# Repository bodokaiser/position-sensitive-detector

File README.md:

# Position-sensitive detector

Position-sensitive detector using the Hamamatsu S5991-01 position-sensitive photodiode.

| Parameter | Value |
| --------- | ----- |
| Spatial resolution | 2 um |
| Bandwidth | 1400 kHz |
| Input voltage | +- 15 V |
| Output voltage | +- 12 V |

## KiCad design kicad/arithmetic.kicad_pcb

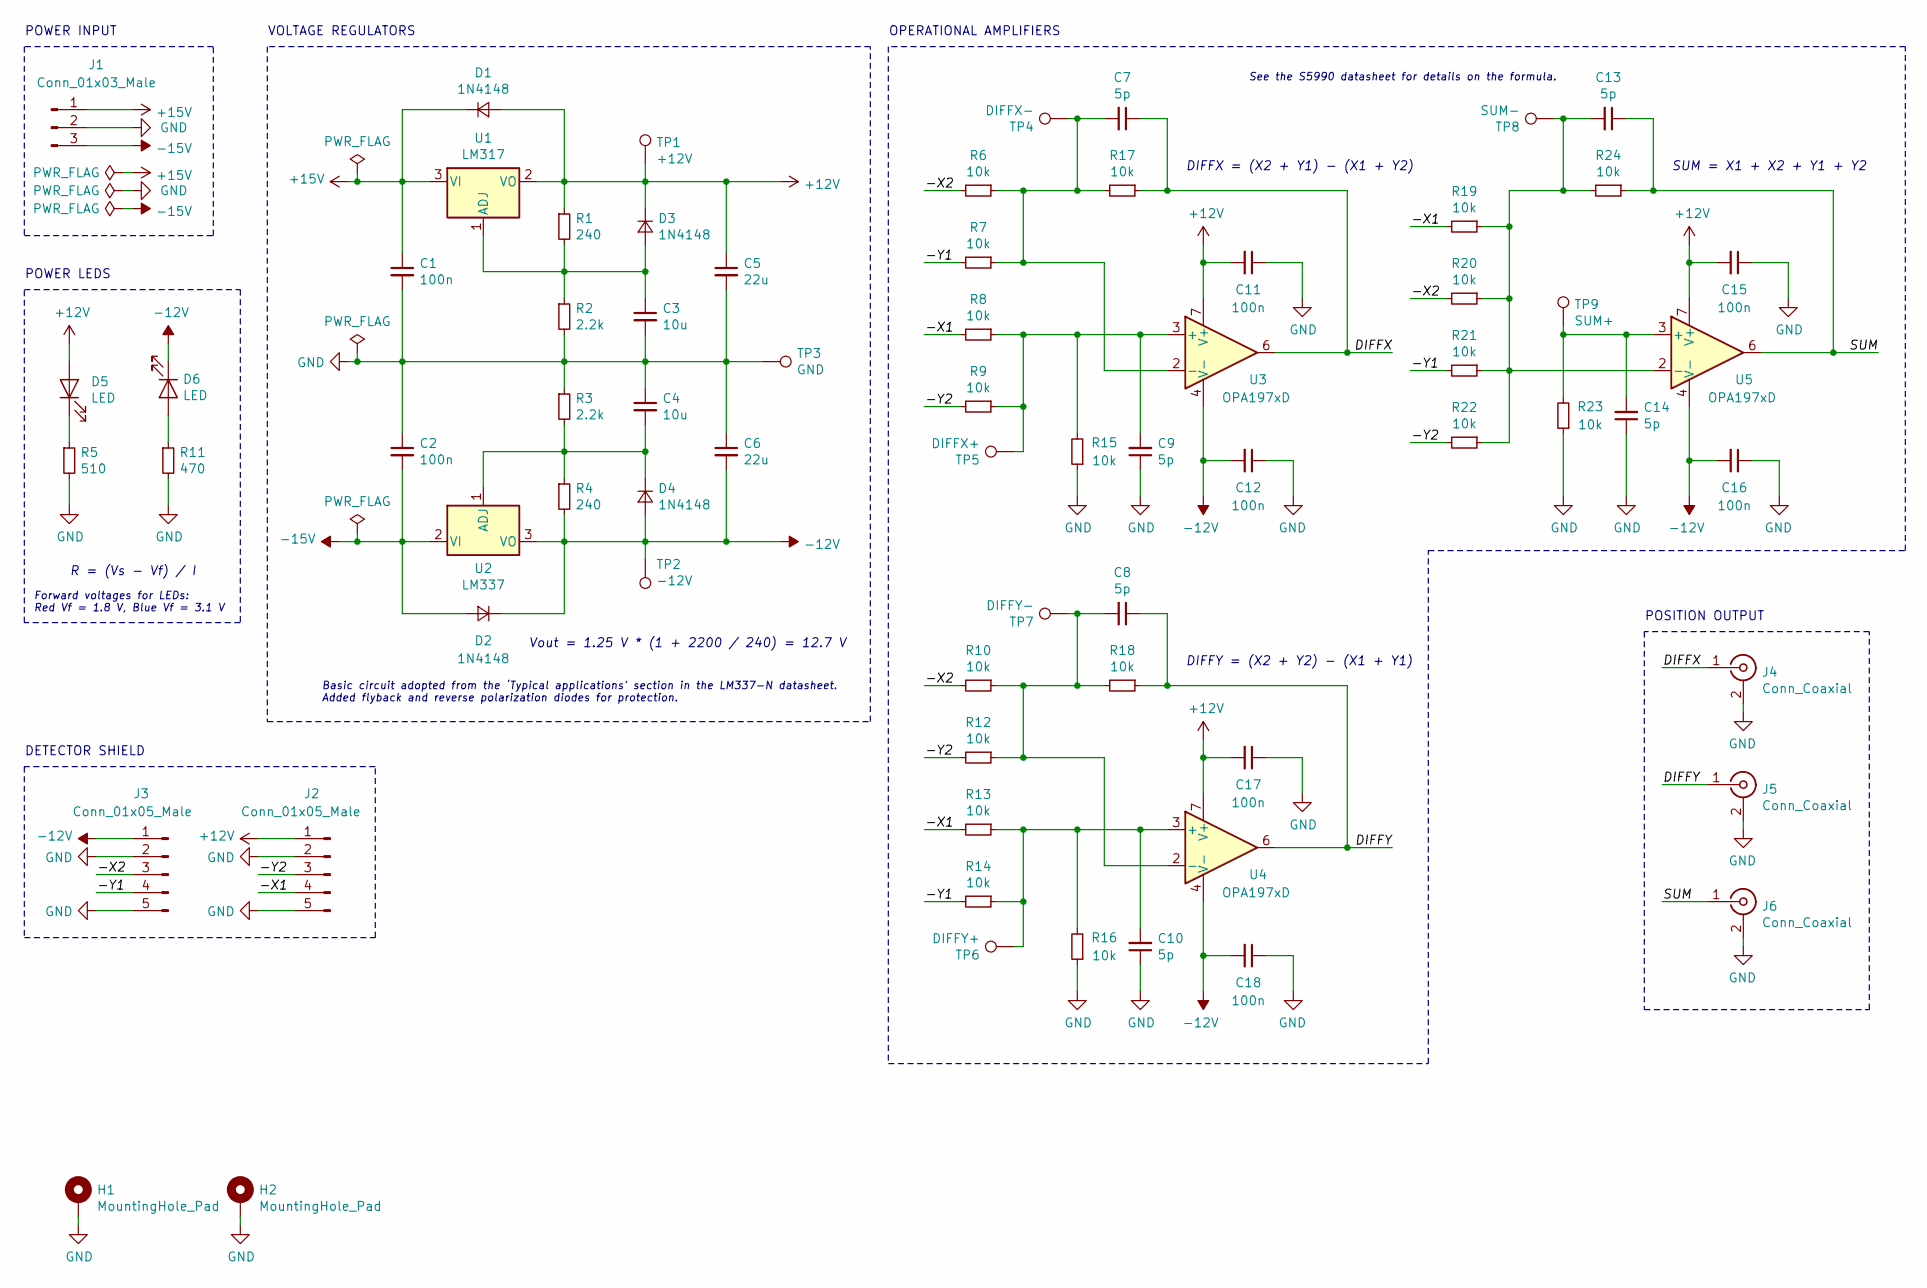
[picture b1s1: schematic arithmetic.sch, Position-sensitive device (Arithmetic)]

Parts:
C1, C2, C11, C12, C15, C16, C17, C18: 100n; C_0603_1608Metric
C3, C4: 10u; C_1210_3225Metric
C5, C6: 22u; C_1210_3225Metric
C7, C8, C9, C10, C13, C14: 5p; C_0603_1608Metric
D1, D2, D3, D4: 1N4148; D_SOD-123
D5, D6: LED; LED_0603_1608Metric
H1, H2: MountingHole_Pad; MountingHole_2.7mm_M2.5_Pad
J1: Conn_01x03_Male; FanPinHeader_1x03_P2.54mm_Vertical
J2, J3: Conn_01x05_Male; PinHeader_1x05_P2.54mm_Vertical
J4, J5, J6: Conn_Coaxial; SMA_Molex_73251-2120_EdgeMount
R1, R4: 240; R_1210_3225Metric
R2, R3: 2.2k; R_1210_3225Metric
R5: 510; R_0603_1608Metric
R6, R7, R8, R9, R10, R12, R13, R14, R15, R16, R17, R18, R19, R20, R21, R22, R23, R24: 10k; R_0603_1608Metric
R11: 470; R_0603_1608Metric
TP1: +12V; TestPoint_Pad_D1.0mm
TP2: -12V; TestPoint_Pad_D1.0mm
TP3: GND; TestPoint_Pad_D1.0mm
TP4: DIFFX-; TestPoint_Pad_D1.0mm
TP5: DIFFX+; TestPoint_Pad_D1.0mm
TP6: DIFFY+; TestPoint_Pad_D1.0mm
TP7: DIFFY-; TestPoint_Pad_D1.0mm
TP8: SUM-; TestPoint_Pad_D1.0mm
TP9: SUM+; TestPoint_Pad_D1.0mm
U1: LM317; SOT-223-3_TabPin2
U2: LM337; SOT-223-3_TabPin2
U3, U4, U5: OPA197xD; SOIC-8_3.9x4.9mm_P1.27mm

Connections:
+12V: C5.1, C11.2, C15.2, C17.2, D1.2 (A), D3.1 (K), D5.2 (A), J2.1, R1.1, TP1.1, U1.2 (VO), U3.7 (V+), U4.7 (V+), U5.7 (V+); also elsewhere on the board
+15V: C1.1, D1.1 (K), J1.1, U1.3 (VI)
-12V: C6.2, C12.2, C16.2, C18.2, D2.1 (K), D4.2 (A), D6.1 (K), J3.1, R4.2, TP2.1, U2.3 (VO), U3.4 (V-), U4.4 (V-), U5.4 (V-); also elsewhere on the board
-15V: C2.2, D2.2 (A), J1.3, U2.2 (VI)
/-X1: J2.4, R8.2, R13.2, R19.2
/-X2: J3.3, R6.2, R10.2, R20.2
/-Y1: J3.4, R7.2, R14.2, R21.2
/-Y2: J2.3, R9.2, R12.2, R22.2
/DIFFX: C7.1, J4.1 (In), R17.1, U3.6
/DIFFY: C8.1, J5.1 (In), R18.1, U4.6
/SUM: C13.1, J6.1 (In), R24.1, U5.6
GND: C1.2, C2.1, C3.2, C4.1, C5.2, C6.1, C9.1, C10.1, C11.1, C12.1, C14.1, C15.1, C16.1, C17.1, C18.1, H1.1, H2.1, J1.2, J2.2, J2.5, J3.2, J3.5, J4.2 (Ext), J5.2 (Ext), J6.2 (Ext), R2.2, R3.1, R5.2, R11.2, R15.1, R16.1, R23.1, TP3.1; also elsewhere on the board
unnamed: C3.1, D3.2 (A), R1.2, R2.1, U1.1 (ADJ)
unnamed: C4.2, D4.1 (K), R3.2, R4.1, U2.1 (ADJ)
unnamed: C7.2, R6.1, R7.1, R17.2, TP4.1, U3.2 (-)
unnamed: C8.2, R10.1, R12.1, R18.2, TP7.1, U4.2 (-)
unnamed: C9.2, R8.1, R9.1, R15.2, TP5.1, U3.3 (+)
unnamed: C10.2, R13.1, R14.1, R16.2, TP6.1, U4.3 (+)
unnamed: C13.2, R19.1, R20.1, R21.1, R22.1, R24.2, TP8.1, U5.2 (-)
unnamed: C14.2, R23.2, TP9.1, U5.3 (+)
unnamed: D5.1 (K), R5.1
unnamed: D6.2 (A), R11.1

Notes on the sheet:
DIFFX = (X2 + Y1) - (X1 + Y2)
SUM = X1 + X2 + Y1 + Y2
See the S5990 datasheet for details on the formula.
VOLTAGE REGULATORS
Vout = 1.25 V * (1 + 2200 / 240) = 12.7 V
Basic circuit adopted from the ‘Typical applications’ section in the LM337-N datasheet. Added flyback and reverse polarization diodes for protection.
DIFFY = (X2 + Y2) - (X1 + Y1)
DETECTOR SHIELD
POSITION OUTPUT
POWER INPUT
OPERATIONAL AMPLIFIERS
Forward voltages for LEDs: Red Vf = 1.8 V, Blue Vf = 3.1 V
R = (Vs - Vf) / I
POWER LEDS

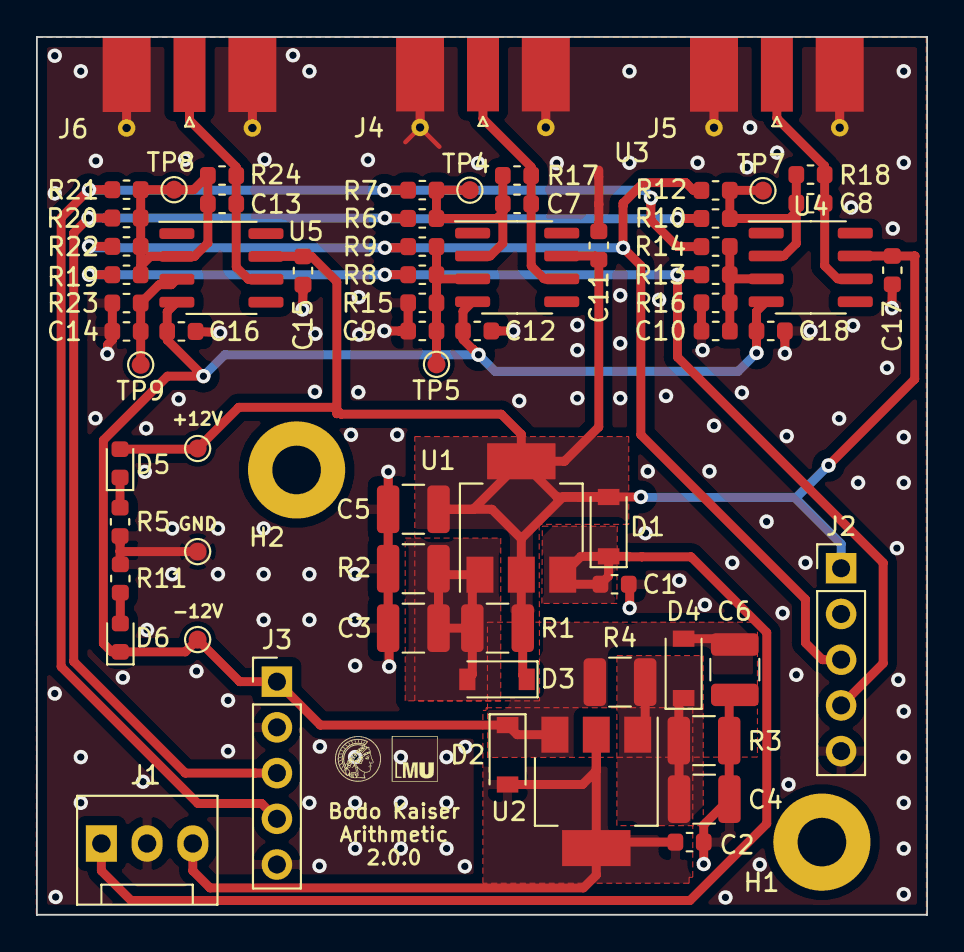
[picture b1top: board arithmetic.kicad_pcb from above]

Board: 2 copper layers, 49.5 x 48.8 mm, 69 parts (0 on the bottom side), 22 nets.

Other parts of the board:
+12V: +12V; TestPoint_Pad_D1.0mm
-12V: -12V; TestPoint_Pad_D1.0mm
GND: GND; TestPoint_Pad_D1.0mm

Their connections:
+12V: +12V.1; also elsewhere on the board
-12V: -12V.1; also elsewhere on the board
GND: GND.1; also elsewhere on the board

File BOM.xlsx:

Value | Footprint | Context | Requirements | Quantity Detector | Quantity Arithmetic | Quantity Total | In Stock | Mouser | Distrelec | RS-Components | Digikey | Comment
100n | C_0603_1608Metric | Decoupling of IC from the voltage supply |  | 6 | 8 | 14 | Yes
18p | C_0603_1608Metric | Feedback capacitance of transimpedance amplifiers | Ultra-low tolerance | 4 |  | 4 | No | https://www.mouser.de/ProductDetail/AVX/06035A180CAT2A?qs=sG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 | Not available | Not available | https://www.digikey.com/products/en?keywords=06035A180CAT2A
1u | C_0603_1608Metric | Voltage regulators / reference |  | 3 |  | 3 | Yes
10n | C_0603_1608Metric | Detector voltage regulator |  | 2 |  | 2 | Yes
22u | C_1210_3225Metric | Voltage regulators / reference |  | 3 | 2 | 5 | Maybe?
10u | C_1210_3225Metric | Voltage regulators / reference |  | 1 | 2 | 3 | Maybe?
5p | C_0603_1608Metric | Feedback capacitance of arithmetic amplifiers | High-precision |  | 6 | 6 | No | https://www.mouser.de/ProductDetail/Murata-Electronics/GCM18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 | Not available | Not available | https://www.digikey.com/products/en?keywords=GCM1885C2A5R0BA16D
6.04k | R_0603_1608Metric | Feedback resistance of transimpedance amplifiers | High-precision | 4 |  | 4 | No | https://www.mouser.de/Passive-Components/Resistors/SMD-Resis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 | Not available | Not available | https://www.digikey.com/product-detail/en/te-connectivity-pa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 | Mouser has better ones but they have long delivery times
100 | R_0603_1608Metric | Low-pass bias voltage reference | Temperature-stable | 1 |  | 1 | Yes
10k | R_0603_1608Metric | Feedback resistance of arithmetic amplifiers | High-precision |  | 18 | 18 | Maybe?
510 | R_0603_1608Metric | LED |  |  | 1 | 1 | Maybe?
470 | R_0603_1608Metric | LED |  |  | 1 | 1 | Maybe?
240 | R_1210_3225Metric | Adjustable voltage regulator | Temperature-stable |  | 2 | 2 | Maybe?
2.2k | R_1210_3225Metric | Adjustable voltage regulator | Temperature-stable |  | 2 | 2 | Maybe?
S599x | S5990 |  |  | 1 |  | 1 | Yes
OPA2197IDx | SOIC-8_3.9x4.9mm_P1.27mm | Transimpedance amplifiers |  | 2 |  | 2 | No | https://www.mouser.de/ProductDetail/Texas-Instruments/OPA219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 | Not available | Not available | https://www.digikey.com/product-detail/en/texas-instruments/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
REF5010ID | SOIC-8_3.9x4.9mm_P1.27mm | Reverse bias voltage reference |  | 1 |  | 1 | No | https://www.mouser.de/ProductDetail/Texas-Instruments/REF501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 | Not available | Not available | https://www.digikey.com/products/en/integrated-circuits-ics/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 | Only Digikey has stocked
LT1761-5 | TSOT-23-5 | Voltage regulator detector |  | 1 |  | 1 | Maybe?
LT1964-5 | TSOT-23-5 | Voltage regulator detector |  | 1 |  | 1 | Maybe?
Conn_01x05_Male | PinSocket_1x05_P2.54mm_Vertical |  |  | 2 |  | 2 | Yes
1N4148 | D_SOD-123 | Voltage regulator arithmetic |  |  | 4 | 4 | Maybe?
LED | LED_0603_1608Metric | Power LED |  |  | 2 | 2 | Yes
OPA197IDx | SOIC-8_3.9x4.9mm_P1.27mm | Arithmetic operational amplifier |  |  | 3 | 3 | No | https://www.mouser.de/ProductDetail/Texas-Instruments/OPA197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 | Not available | https://de.rs-online.com/web/p/operationsverstarker/1977408/
LM317EMP/NOPB | SOT-223-3_TabPin2 | Voltage regulator arithmetic |  |  | 1 | 1 | No | https://www.mouser.de/ProductDetail/Texas-Instruments/LM317E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 | https://www.distrelec.de/en/linear-voltage-regulator-25-37-s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 | Not available | https://www.digikey.com/product-detail/en/texas-instruments/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 | Sometimes they have 1A and sometimes 1.5A output current?
LM337IMP/NOPB | SOT-223-3_TabPin2 | Voltage regulator arithmetic |  |  | 1 | 1 | No | https://www.mouser.de/ProductDetail/Texas-Instruments/LM337I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 | https://www.distrelec.de/en/linear-voltage-regulator-37-sot-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 | https://de.rs-online.com/web/p/spannungsregler/7614612/ | https://www.digikey.com/product-detail/en/texas-instruments/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 | Sometimes they have 1A and sometimes 1.5A output current?
Conn_01x03_Male | FanPinHeader_1x03_P2.54mm_Vertical |  |  |  | 1 | 1 | No | https://www.mouser.de/ProductDetail/Wurth-Elektronik/6190031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 | https://www.distrelec.de/en/pin-header-straight-poles-wuerth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 | https://de.rs-online.com/web/p/leiterplatten-header/8281474/ | https://www.digikey.com/products/en?keywords=61900311121
Conn_01x05_Male | PinHeader_1x05_P2.54mm_Vertical |  |  |  | 2 | 2 | Yes
Conn_Coaxial | SMA_Molex_73251-2120_EdgeMount |  |  |  | 3 | 3 | Yes

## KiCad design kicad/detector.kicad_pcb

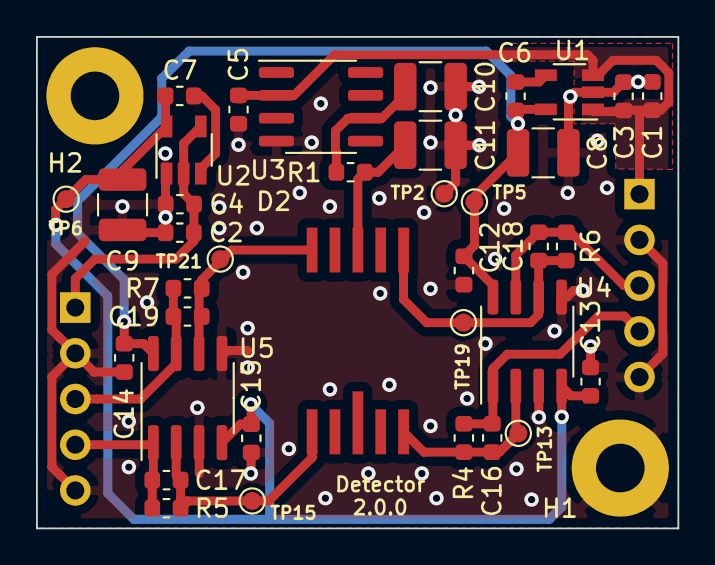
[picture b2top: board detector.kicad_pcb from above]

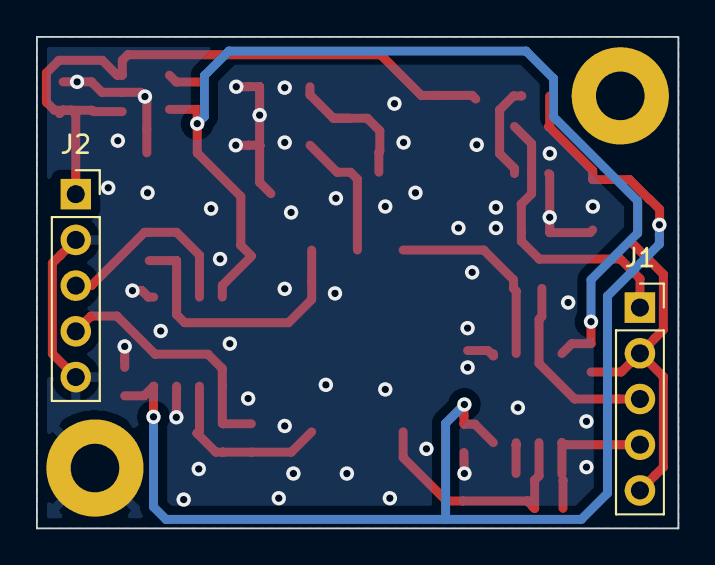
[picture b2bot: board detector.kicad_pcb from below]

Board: 2 copper layers, 35.6 x 27.3 mm, 41 parts (2 on the bottom side), 17 nets.

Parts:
C1, C2, C12, C13, C14, C15: 100n; C_0603_1608Metric
C3, C4, C5: 1u; C_0603_1608Metric
C6, C7: 10n; C_0603_1608Metric
C8, C9, C11: 22u; C_1210_3225Metric
C10: 10u; C_1210_3225Metric
C16, C17, C18, C19: 18p; C_0603_1608Metric
D2: S599x; S5990
H1, H2: MountingHole_Pad; MountingHole_2.7mm_M2.5_Pad
J1, J2: Conn_01x05_Male; PinSocket_1x05_P2.54mm_Vertical
R1: 100; R_0603_1608Metric
R4, R5, R6, R7: 6.04k; R_0603_1608Metric
TP2: GND; TestPoint_Pad_D1.0mm
TP5: +5V; TestPoint_Pad_D1.0mm
TP6: -5V; TestPoint_Pad_D1.0mm
TP13: I1; TestPoint_Pad_D1.0mm
TP15: I3; TestPoint_Pad_D1.0mm
TP19: I4; TestPoint_Pad_D1.0mm
TP21: I2; TestPoint_Pad_D1.0mm
U1: LT1761-5; TSOT-23-5
U2: LT1964-5; TSOT-23-5
U3: REF5010ID; SOIC-8_3.9x4.9mm_P1.27mm
U4, U5: OPA2197xD; SOIC-8_3.9x4.9mm_P1.27mm

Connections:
+5V: C6.2, C8.1, C12.2, C14.2, TP5.1, U1.5, U4.8, U5.8
+12V: C1.1, C3.1, C5.1, J2.1, U1.1, U1.3, U3.2
-5V: C7.1, C9.2, C13.2, C15.2, TP6.1, U2.5, U4.4, U5.4
-12V: C2.2, C4.2, J1.1, U2.2, U2.4
/-X1: C16.1, J2.4, R4.1, U4.1
/-X2: C19.1, J1.3, R7.1, U5.7
/-Y1: C17.1, J1.4, R5.1, U5.1
/-Y2: C18.1, J2.3, R6.1, U4.7
GND: C1.2, C2.1, C3.2, C4.1, C5.2, C8.2, C9.1, C10.2, C11.2, C12.1, C13.1, C14.1, C15.1, H1.1, J1.2, J1.5, J2.2, J2.5, TP2.1, U1.2, U2.1, U3.4, U4.3, U4.5, U5.3, U5.5
unnamed: C6.1, U1.4
unnamed: C7.2, U2.3
unnamed: C10.1, R1.2, U3.6
unnamed: C11.1, D2.8, R1.1
unnamed: C16.2, D2.1, R4.2, TP13.1, U4.2
unnamed: C17.2, D2.5, R5.2, TP15.1, U5.2
unnamed: C18.2, D2.10, R6.2, TP19.1, U4.6
unnamed: C19.2, D2.6, R7.2, TP21.1, U5.6

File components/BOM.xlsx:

Value | Footprint | Context | Requirements | Quantity Detector | Quantity Arithmetic | Quantity Total | In Stock | Part number | Mouser | Distrelec | RS-Components | Digikey | Comment
100n | C_0603_1608Metric | Decoupling of IC from the voltage supply |  | 6 | 8 | 14 | Yes
18p | C_0603_1608Metric | Feedback capacitance of transimpedance amplifiers | Ultra-low tolerance | 4 |  | 4 | No |  | https://www.mouser.de/ProductDetail/AVX/06035A180CAT2A?qs=sG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 | Not available | Not available | https://www.digikey.com/products/en?keywords=06035A180CAT2A
1u | C_0603_1608Metric | Voltage regulators / reference |  | 3 |  | 3 | Yes
10n | C_0603_1608Metric | Detector voltage regulator |  | 2 |  | 2 | Yes
22u | C_1210_3225Metric | Voltage regulators / reference |  | 3 | 2 | 5 | Low | TMK316BBJ226ML-T
10u | C_1210_3225Metric | Voltage regulators / reference |  | 1 | 2 | 3 | No
5p | C_0603_1608Metric | Feedback capacitance of arithmetic amplifiers | High-precision |  | 6 | 6 | Low | CBR06C509A5GAC | https://www.mouser.de/ProductDetail/KEMET/CBR06C509A5GAC?qs=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 | Not available | Not available | https://www.digikey.com/product-detail/en/kemet/CBR06C509A5G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
6.04k | R_0603_1608Metric | Feedback resistance of transimpedance amplifiers | High-precision | 4 |  | 4 | Yes |  | https://www.mouser.de/Passive-Components/Resistors/SMD-Resis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 | Not available | Not available | https://www.digikey.com/product-detail/en/te-connectivity-pa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 | Mouser has better ones but they have long delivery times
100 | R_0603_1608Metric | Low-pass bias voltage reference | Temperature-stable | 1 |  | 1 | Yes
10k | R_0603_1608Metric | Feedback resistance of arithmetic amplifiers | High-precision |  | 18 | 18 | Yes
510 | R_1210_3225Metric | Power LED |  |  | 1 | 1 | No
470 | R_1210_3225Metric | Power LED |  |  | 1 | 1 | No
240 | R_1210_3225Metric | Adjustable voltage regulator | Temperature-stable |  | 2 | 2 | No
2.2k | R_1210_3225Metric | Adjustable voltage regulator | Temperature-stable |  | 2 | 2 | No
S599x | S5990 |  |  | 1 |  | 1 | Yes
OPA2197IDx | SOIC-8_3.9x4.9mm_P1.27mm | Transimpedance amplifiers |  | 2 |  | 2 | Yes |  | https://www.mouser.de/ProductDetail/Texas-Instruments/OPA219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 | Not available | Not available | https://www.digikey.com/product-detail/en/texas-instruments/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
REF5010ID | SOIC-8_3.9x4.9mm_P1.27mm | Reverse bias voltage reference |  | 1 |  | 1 | Yes |  | https://www.mouser.de/ProductDetail/Texas-Instruments/REF501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 | Not available | Not available | https://www.digikey.com/products/en/integrated-circuits-ics/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 | Only Digikey has stocked
LT1761-5 | TSOT-23-5 | Voltage regulator detector |  | 1 |  | 1 | Yes
LT1964-5 | TSOT-23-5 | Voltage regulator detector |  | 1 |  | 1 | Yes
Conn_01x05_Male | PinSocket_1x05_P2.54mm_Vertical |  |  | 2 |  | 2 | Yes
1N4148 | D_SOD-123 | Voltage regulator arithmetic |  |  | 4 | 4 | Yes
LED | LED_0603_1608Metric | Power LED |  |  | 2 | 2 | Yes
OPA197IDx | SOIC-8_3.9x4.9mm_P1.27mm | Arithmetic operational amplifier |  |  | 3 | 3 | Yes |  | https://www.mouser.de/ProductDetail/Texas-Instruments/OPA197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 | Not available | https://de.rs-online.com/web/p/operationsverstarker/1977408/
LM317EMP/NOPB | SOT-223-3_TabPin2 | Voltage regulator arithmetic |  |  | 1 | 1 | Yes |  | https://www.mouser.de/ProductDetail/Texas-Instruments/LM317E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 | https://www.distrelec.de/en/linear-voltage-regulator-25-37-s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 | Not available | https://www.digikey.com/product-detail/en/texas-instruments/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 | Sometimes they have 1A and sometimes 1.5A output current?
LM337IMP/NOPB | SOT-223-3_TabPin2 | Voltage regulator arithmetic |  |  | 1 | 1 | Yes |  | https://www.mouser.de/ProductDetail/Texas-Instruments/LM337I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 | https://www.distrelec.de/en/linear-voltage-regulator-37-sot-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 | https://de.rs-online.com/web/p/spannungsregler/7614612/ | https://www.digikey.com/product-detail/en/texas-instruments/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 | Sometimes they have 1A and sometimes 1.5A output current?
Conn_01x03_Male | FanPinHeader_1x03_P2.54mm_Vertical |  |  |  | 1 | 1 | Yes |  | https://www.mouser.de/ProductDetail/Wurth-Elektronik/6190031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 | https://www.distrelec.de/en/pin-header-straight-poles-wuerth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 | https://de.rs-online.com/web/p/leiterplatten-header/8281474/ | https://www.digikey.com/products/en?keywords=61900311121
Conn_01x05_Male | PinHeader_1x05_P2.54mm_Vertical |  |  |  | 2 | 2 | Yes
Conn_Coaxial | SMA_Molex_73251-2120_EdgeMount |  |  |  | 3 | 3 | Yes
 | 1x03 PinHeader Steckverbinder Female

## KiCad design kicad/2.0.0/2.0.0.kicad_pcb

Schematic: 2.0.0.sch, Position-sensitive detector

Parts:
C1, C2, C3, C4, C5, C6, C15, C16, C17, C18: 100n; C_0603_1608Metric
C7, C8: 10u; C_1206_3216Metric
C9, C10, C13, C14: 18p; C_0603_1608Metric
C11, C12: 1u; C_0603_1608Metric
D1: S599x; S5990
J1: DIFFX; SMA_Molex_73251-2120_EdgeMount
J2: DIFFY; SMA_Molex_73251-2120_EdgeMount
J3: POWER; TerminalBlock_TE_282834-3_1x03_P2.54mm_Horizontal
J4: SUM; SMA_Molex_73251-2120_EdgeMount
R1, R4: 120; R_0603_1608Metric
R2, R3: 1.1k; R_0603_1608Metric
R5, R6, R7, R8: 6k; R_0603_1608Metric
R9, R10, R11, R12, R13, R14, R15, R16, R17, R18, R19, R20, R21, R22, R23, R24, R25, R26: 1k; R_0603_1608Metric
U1, U2, U5: OPA2197IDR; SOIC-8_3.9x4.9mm_P1.27mm
U3: LM317; SOT-223-3_TabPin2
U4: LM337; SOT-223-3_TabPin2
U6: OPA197IDR; SOIC-8_3.9x4.9mm_P1.27mm

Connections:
+12V: C1.2, C3.2, C11.1, C15.2, C17.2, D1.8 (Cathode), R1.1, U1.8, U2.8, U3.2 (VO), U5.8, U6.7
+15V: C5.1, J3.1, U3.3 (VI)
-12V: C2.2, C4.2, C12.2, C16.2, C18.2, R4.2, U1.4, U2.4, U4.3 (VO), U5.4, U6.4
-15V: C6.2, J3.3, U4.2 (VI)
/-X1: C9.1, R5.1, R11.2, R15.2, R21.2, U1.1
/-X2: C14.1, R8.1, R9.2, R13.2, R22.2, U2.7
/-Y1: C10.1, R6.1, R10.2, R16.2, R23.2, U2.1
/-Y2: C13.1, R7.1, R12.2, R14.2, R24.2, U1.7
/DIFFX: J1.1 (In), R17.1, U5.1
/DIFFY: J2.1 (In), R19.1, U5.7
/SUM: J4.1 (In), R26.1, U6.6
GND: C1.1, C2.1, C3.1, C4.1, C5.2, C6.1, C7.2, C8.1, C11.2, C12.1, C15.1, C16.1, C17.1, C18.1, J1.2 (Ext), J2.2 (Ext), J3.2, J4.2 (Ext), R2.2, R3.1, R18.1, R20.1, R25.2, U1.3, U1.5, U2.3, U2.5
unnamed: C7.1, R1.2, R2.1, U3.1 (ADJ)
unnamed: C8.2, R3.2, R4.1, U4.1 (ADJ)
unnamed: C9.2, D1.1 (X1), R5.2, U1.2
unnamed: C10.2, D1.5 (Anode_Y1), R6.2, U2.2
unnamed: C13.2, D1.10 (Anode_Y2), R7.2, U1.6
unnamed: C14.2, D1.6 (Anode_X2), R8.2, U2.6
unnamed: R9.1, R10.1, R17.2, U5.2
unnamed: R11.1, R12.1, R18.2, U5.3
unnamed: R13.1, R14.1, R19.2, U5.6
unnamed: R15.1, R16.1, R20.2, U5.5
unnamed: R21.1, R22.1, R23.1, R24.1, R26.2, U6.2
unnamed: R25.1, U6.3

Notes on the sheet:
POWER CONNECTOR
See section ‘Typical applications’ in the LM337-N datasheet.
Vout = 1.25 V * (1 + R / 120)
VOLTAGE REGULATORS
Reverse bias voltage
DETECTOR AND TRANSIMPEDANCE AMPLIFIERS
For details on how to size the feedback capacitor check W. Jung. Opamp Application Handbook. p. 273
Vout = -Rf * Iphoto < -4 V
Cin = Cpd + Ccm + Cdf = (90 + 6.4 + 1.6) pF = 98 pF
Cf = (C1 / (2 * pi * Rf * GBP))^(1/2) < 18 pF
DIFFERENCE AMPLIFIERS
DIFFX = (X2 + Y1) - (X1 + Y2) DIFFY = (X2 + Y2) - (X1 + Y1)
See the S5990 datasheet for details on the formula.
SUM = X1 + X2 + Y1 + Y2
SUMMATION AMPLIFIER
OUTPUT CONNECTORS

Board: 2 copper layers, 55 parts (0 on the bottom side), 24 nets, no tracks yet.

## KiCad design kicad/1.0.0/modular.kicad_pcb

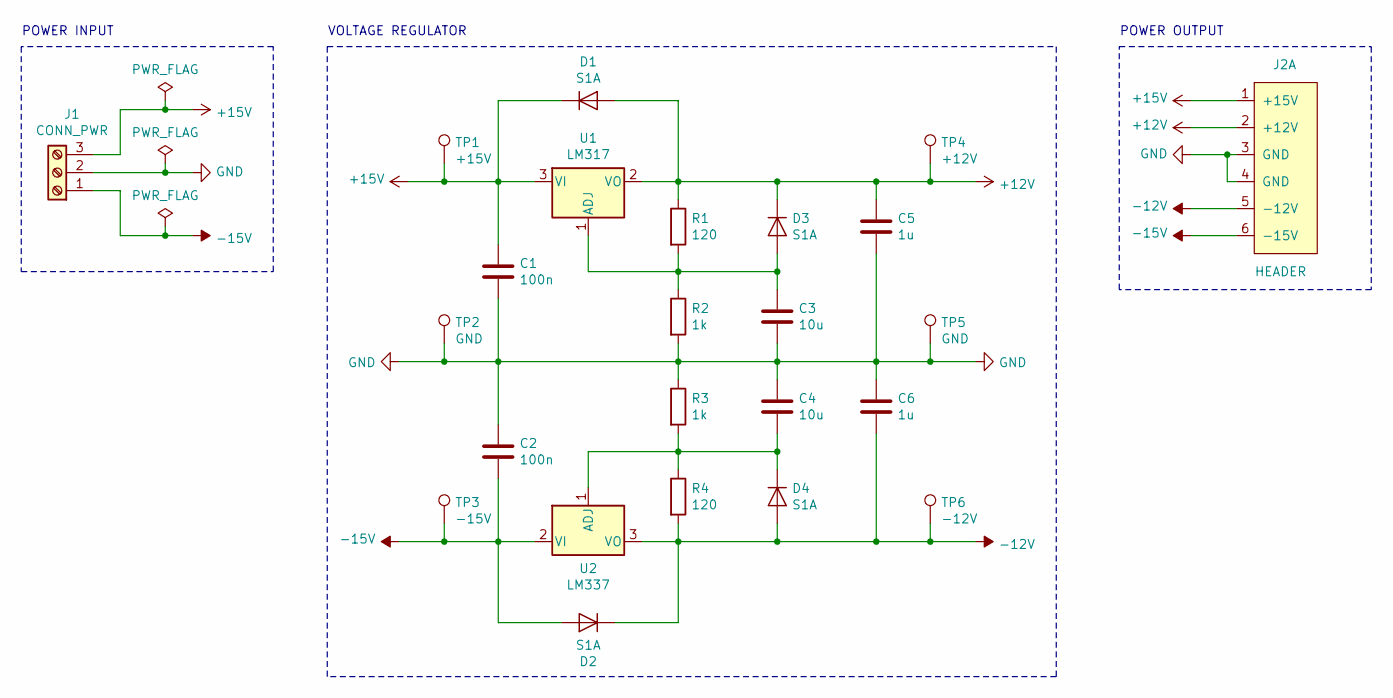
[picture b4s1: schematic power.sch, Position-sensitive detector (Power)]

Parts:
C1, C2: 100n; C_0603_1608Metric
C3, C4: 10u; C_0603_1608Metric
C5, C6: 1u; C_0603_1608Metric
D1, D2, D3, D4: S1A; D_SMA
J1: CONN_PWR; TerminalBlock_TE_282834-3_1x03_P2.54mm_Horizontal
J2: HEADER; PinHeader_2.54mm
R1, R4: 120; R_0603_1608Metric
R2, R3: 1k; R_0603_1608Metric
TP1: +15V; TestPoint_THTPad_D1.0mm_Drill0.5mm
TP2, TP5: GND; TestPoint_THTPad_D1.0mm_Drill0.5mm
TP3: -15V; TestPoint_THTPad_D1.0mm_Drill0.5mm
TP4: +12V; TestPoint_THTPad_D1.0mm_Drill0.5mm
TP6: -12V; TestPoint_THTPad_D1.0mm_Drill0.5mm
U1: LM317; SOT-223-3_TabPin2
U2: LM337; SOT-223-3_TabPin2

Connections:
+12V: C5.1, D1.2 (A), D3.1 (K), J2.2 (+12V), R1.1, TP4.1, U1.2 (VO); also elsewhere on the board
+15V: C1.1, D1.1 (K), J1.3, J2.1 (+15V), TP1.1, U1.3 (VI); also elsewhere on the board
-12V: C6.2, D2.1 (K), D4.2 (A), J2.5 (-12V), R4.2, TP6.1, U2.3 (VO); also elsewhere on the board
-15V: C2.2, D2.2 (A), J1.1, J2.6 (-15V), TP3.1, U2.2 (VI)
GND: C1.2, C2.1, C3.2, C4.1, C5.2, C6.1, J1.2, J2.3 (GND), J2.4 (GND), R2.2, R3.1, TP2.1, TP5.1; also elsewhere on the board
unnamed: C3.1, D3.2 (A), R1.2, R2.1, U1.1 (ADJ)
unnamed: C4.2, D4.1 (K), R3.2, R4.1, U2.1 (ADJ)

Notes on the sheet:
POWER INPUT
VOLTAGE REGULATOR
POWER OUTPUT

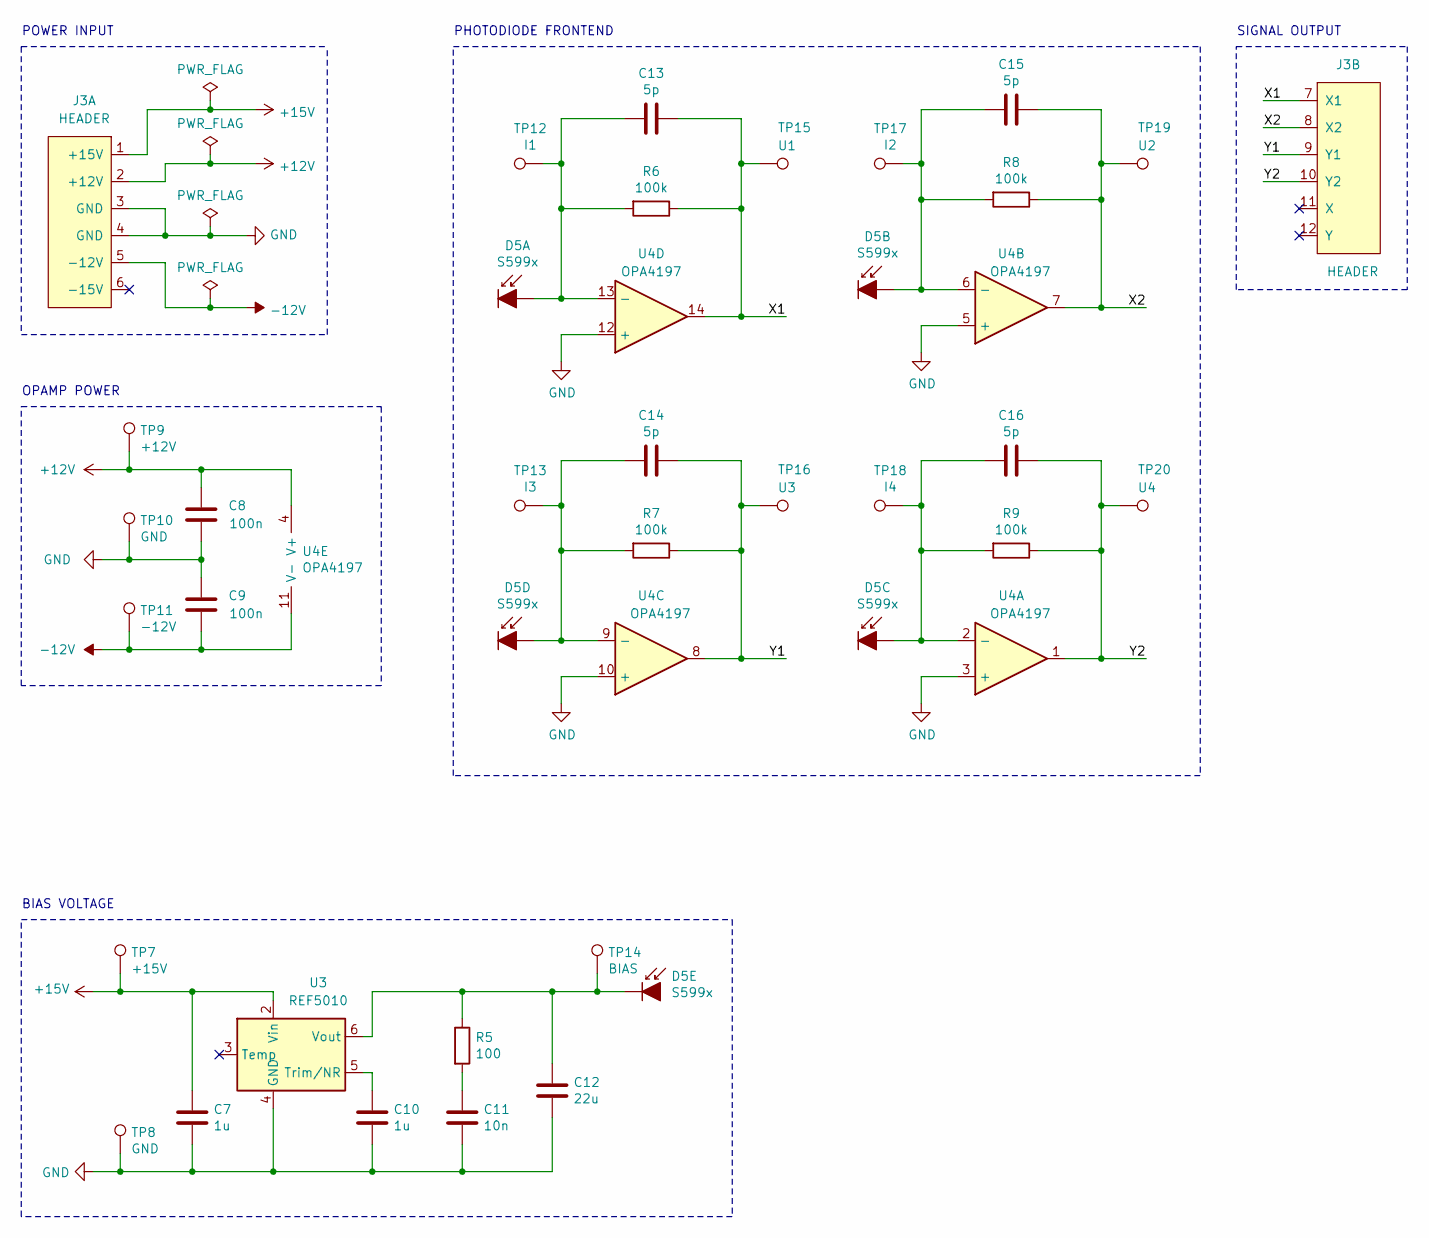
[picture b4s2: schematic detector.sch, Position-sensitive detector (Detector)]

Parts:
C7, C10: 1u; C_0603_1608Metric
C8, C9: 100n; C_0603_1608Metric
C11: 10n; C_0603_1608Metric
C12: 22u; C_0603_1608Metric
C13, C14, C15, C16: 5p; C_0603_1608Metric
D5: S599x; S5990
J3: HEADER; PinHeader_2.54mm
R5: 100; R_0603_1608Metric
R6, R7, R8, R9: 100k; R_0603_1608Metric
TP7: +15V; TestPoint_THTPad_D1.0mm_Drill0.5mm
TP8, TP10: GND; TestPoint_THTPad_D1.0mm_Drill0.5mm
TP9: +12V; TestPoint_THTPad_D1.0mm_Drill0.5mm
TP11: -12V; TestPoint_THTPad_D1.0mm_Drill0.5mm
TP12: I1; TestPoint_THTPad_D1.0mm_Drill0.5mm
TP13: I3; TestPoint_THTPad_D1.0mm_Drill0.5mm
TP14: BIAS; TestPoint_THTPad_D1.0mm_Drill0.5mm
TP15: U1; TestPoint_THTPad_D1.0mm_Drill0.5mm
TP16: U3; TestPoint_THTPad_D1.0mm_Drill0.5mm
TP17: I2; TestPoint_THTPad_D1.0mm_Drill0.5mm
TP18: I4; TestPoint_THTPad_D1.0mm_Drill0.5mm
TP19: U2; TestPoint_THTPad_D1.0mm_Drill0.5mm
TP20: U4; TestPoint_THTPad_D1.0mm_Drill0.5mm
U3: REF5010; SOIC-8_3.9x4.9mm_P1.27mm
U4: OPA4197; TSSOP-14_4.4x5mm_P0.65mm

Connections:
+12V: C8.2, J3.2 (+12V), TP9.1, U4.4 (V+); also elsewhere on the board
+15V: C7.1, J3.1 (+15V), TP7.1, U3.2 (Vin); also elsewhere on the board
-12V: C9.1, J3.5 (-12V), TP11.1, U4.11 (V-); also elsewhere on the board
/Detector/X1: C13.1, J3.7 (X1), R6.1, TP15.1, U4.14
/Detector/X2: C15.1, J3.8 (X2), R8.1, TP19.1, U4.7
/Detector/Y1: C14.1, J3.9 (Y1), R7.1, TP16.1, U4.8
/Detector/Y2: C16.1, J3.10 (Y2), R9.1, TP20.1, U4.1
GND: C7.2, C8.1, C9.2, C10.2, C11.2, C12.2, J3.3 (GND), J3.4 (GND), TP8.1, TP10.1, U3.4 (GND), U4.3 (+), U4.5 (+), U4.10 (+), U4.12 (+); also elsewhere on the board
unnamed: C10.1, U3.5 (Trim/NR)
unnamed: C11.1, R5.2
unnamed: C12.1, D5.8 (K), R5.1, TP14.1, U3.6 (Vout)
unnamed: C13.2, D5.1 (I1), R6.2, TP12.1, U4.13 (-)
unnamed: C14.2, D5.5 (I3), R7.2, TP13.1, U4.9 (-)
unnamed: C15.2, D5.6 (I2), R8.2, TP17.1, U4.6 (-)
unnamed: C16.2, D5.10 (I4), R9.2, TP18.1, U4.2 (-)

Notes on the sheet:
PHOTODIODE FRONTEND
SIGNAL OUTPUT
POWER INPUT
BIAS VOLTAGE
OPAMP POWER

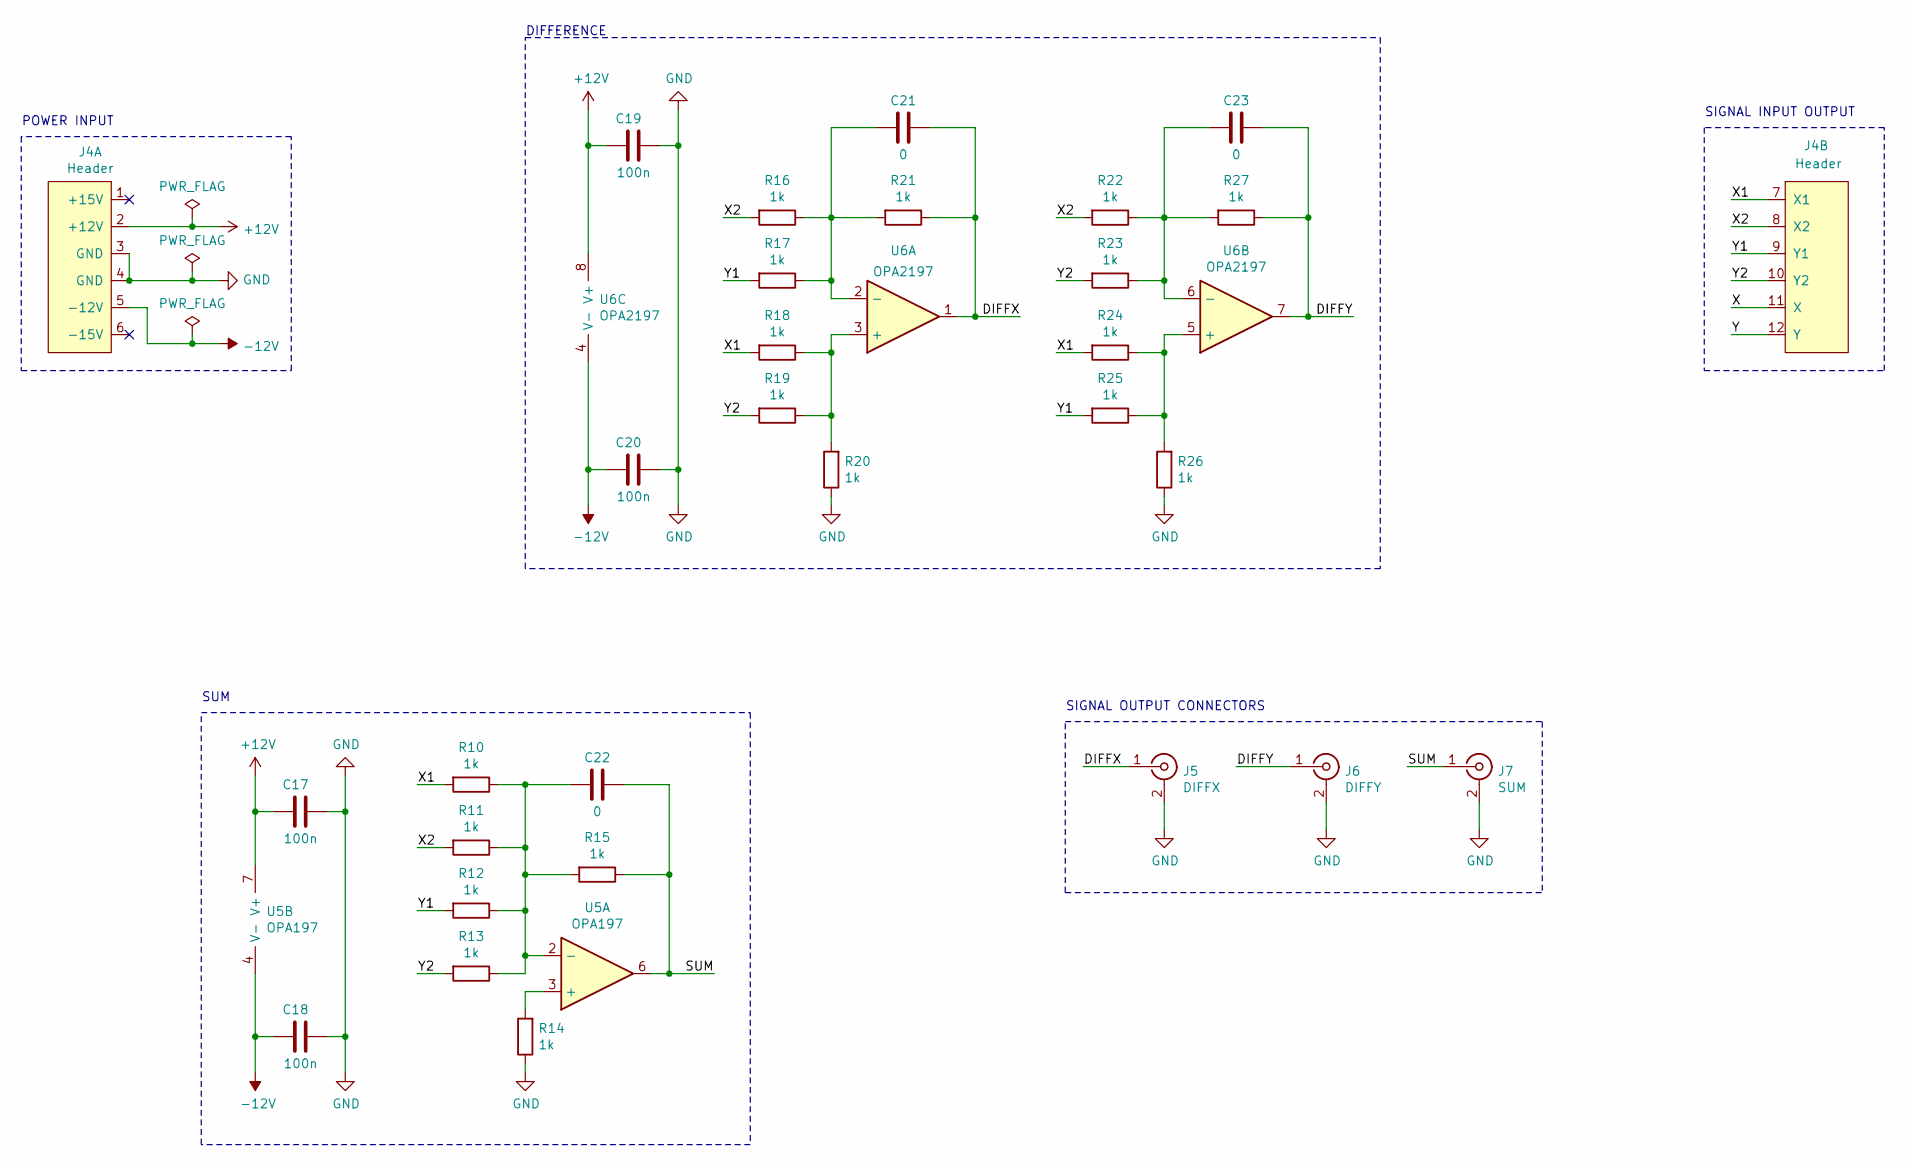
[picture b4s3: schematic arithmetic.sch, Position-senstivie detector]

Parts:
C17, C18, C19, C20: 100n; C_0603_1608Metric
C21, C22, C23: 0; C_0603_1608Metric
J4: Header; PinHeader_2.54mm
J5: DIFFX; SMA_Molex_73251-2120_EdgeMount
J6: DIFFY; SMA_Molex_73251-2120_EdgeMount
J7: SUM; SMA_Molex_73251-2120_EdgeMount
R10, R11, R12, R13, R14, R15, R16, R17, R18, R19, R20, R21, R22, R23, R24, R25, R26, R27: 1k; R_0603_1608Metric
U5: OPA197; SOIC-8_3.9x4.9mm_P1.27mm
U6: OPA2197; SOIC-8_3.9x4.9mm_P1.27mm

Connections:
+12V: C17.1, C19.1, J4.2 (+12V), U5.7 (V+), U6.8 (V+); also elsewhere on the board
-12V: C18.1, C20.1, J4.5 (-12V), U5.4 (V-), U6.4 (V-); also elsewhere on the board
/Arithmetic/DIFFX: C21.1, J5.1 (In), R21.1, U6.1; also elsewhere on the board
/Arithmetic/DIFFY: C23.1, J6.1 (In), R27.1, U6.7; also elsewhere on the board
/Arithmetic/SUM: C22.1, J7.1 (In), R15.1, U5.6; also elsewhere on the board
/Arithmetic/X: J4.11 (X)
/Arithmetic/X1: J4.7 (X1), R10.2, R18.2, R24.2
/Arithmetic/X2: J4.8 (X2), R11.2, R16.2, R22.2
/Arithmetic/Y: J4.12 (Y)
/Arithmetic/Y1: J4.9 (Y1), R12.2, R17.2, R25.2
/Arithmetic/Y2: J4.10 (Y2), R13.2, R19.2, R23.2
GND: C17.2, C18.2, C19.2, C20.2, J4.3 (GND), J4.4 (GND), J5.2 (Ext), J6.2 (Ext), J7.2 (Ext), R14.1, R20.1, R26.1; also elsewhere on the board
unnamed: C21.2, R16.1, R17.1, R21.2, U6.2 (-)
unnamed: C22.2, R10.1, R11.1, R12.1, R13.1, R15.2, U5.2 (-)
unnamed: C23.2, R22.1, R23.1, R27.2, U6.6 (-)
unnamed: R14.2, U5.3 (+)
unnamed: R18.1, R19.1, R20.2, U6.3 (+)
unnamed: R24.1, R25.1, R26.2, U6.5 (+)

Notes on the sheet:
POWER INPUT
DIFFERENCE
SIGNAL INPUT OUTPUT
SUM
SIGNAL OUTPUT CONNECTORS

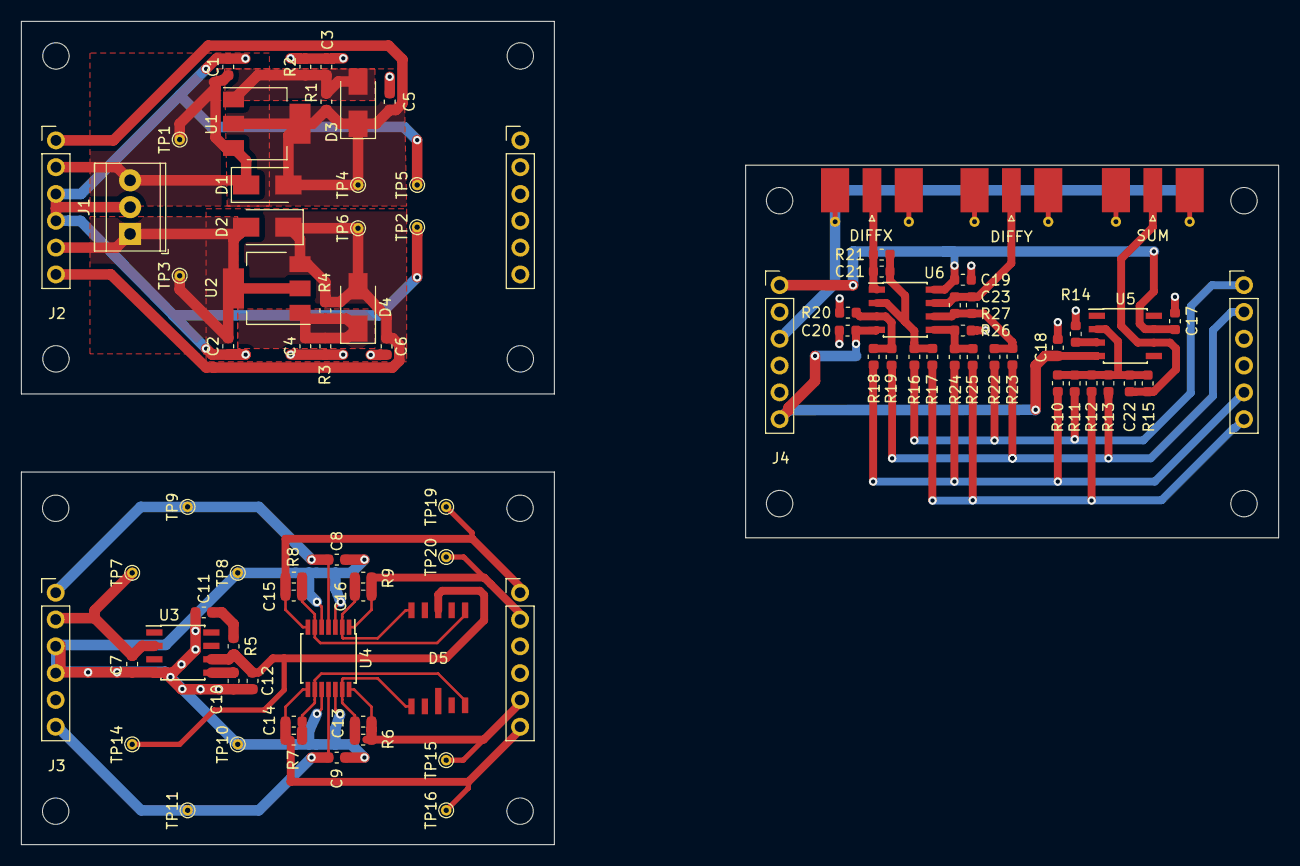
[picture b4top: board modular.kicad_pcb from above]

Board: 2 copper layers, 119.1 x 78.0 mm, 84 parts (0 on the bottom side), 31 nets.

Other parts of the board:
DIFFX: DIFFX; SMA_Molex_73251-2120_EdgeMount
DIFFY: DIFFY; SMA_Molex_73251-2120_EdgeMount
SUM: SUM; SMA_Molex_73251-2120_EdgeMount

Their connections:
/Arithmetic/DIFFX: DIFFX.1; also elsewhere on the board
/Arithmetic/DIFFY: DIFFY.1; also elsewhere on the board
/Arithmetic/SUM: SUM.1; also elsewhere on the board
GND: DIFFX.2, DIFFY.2, SUM.2; also elsewhere on the board
